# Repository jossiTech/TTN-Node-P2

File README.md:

# TTN-Node-P2
Based on Arduino Pro Micro 3.3V & RFM95W:  four 1-Wire-Busses - suitable enclosure available - messure Temperature, Humidity, ...

read more on the [Wiki](https://github.com/jossiTech/TTN-Node-P2/wiki)

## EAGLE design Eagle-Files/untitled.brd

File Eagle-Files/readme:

If you are interested in the original EAGLE-Files (*.brd and *.sch) feel free to contact me (info@jossitech.de)...
A suitable case is available in which the PCB fits perfectly. Search for "strapubox 524"

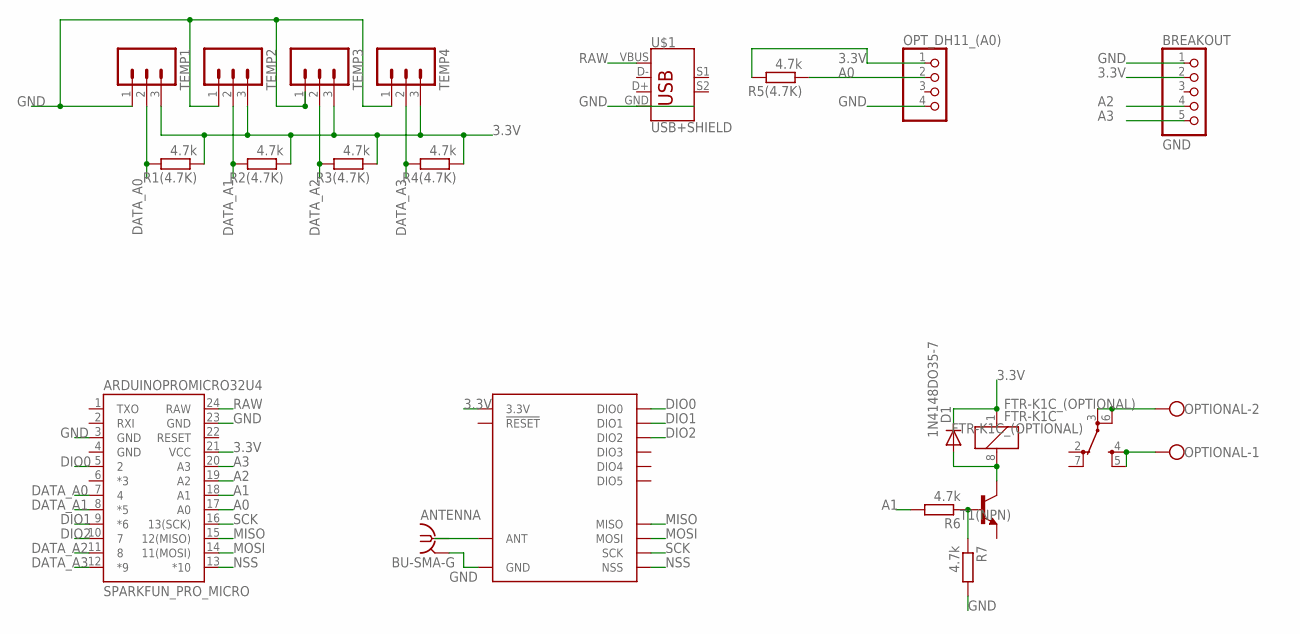
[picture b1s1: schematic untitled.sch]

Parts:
ANTENNA: BU-SMA-G
ARDUINOPROMICRO32U4: SPARKFUN_PRO_MICRO
BREAKOUT: GND; 1X05
D1: 1N4148DO35-7; DO35-7
FTR-K1C_(OPTIONAL): FTR-K1C
OPTIONAL: W237-102
OPT_DH11_(A0): PINHD-1X4; 1X04
R1(4.7K), R2(4.7K), R3(4.7K), R4(4.7K), R5(4.7K), R6, R7: 4.7k; 0207/10
T1(NPN): BC237-NPN-TO92-CBE; TO92-CBE
TEMP1, TEMP2, TEMP3, TEMP4: M03; 03P
U2: RFM95W; RFM95/96/97/98W
U$1: USB+SHIELD; USB-B-PTH

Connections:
3.3V: ARDUINOPROMICRO32U4.21 (VCC), BREAKOUT.2, D1.C, FTR-K1C_(OPTIONAL).1, OPT_DH11_(A0).1, R1(4.7K).1, R2(4.7K).1, R3(4.7K).1, R4(4.7K).1, R5(4.7K).2, TEMP1.3, TEMP2.3, TEMP3.3, TEMP4.3, U2.3.3V
A0: ARDUINOPROMICRO32U4.17 (A0), OPT_DH11_(A0).2, R5(4.7K).1
A1: ARDUINOPROMICRO32U4.18 (A1), R6.2
A2: ARDUINOPROMICRO32U4.19 (A2), BREAKOUT.4
A3: ARDUINOPROMICRO32U4.20 (A3), BREAKOUT.5
DATA_A0: ARDUINOPROMICRO32U4.7 (4), R1(4.7K).2, TEMP1.2
DATA_A1: ARDUINOPROMICRO32U4.8 (*5), R2(4.7K).2, TEMP2.2
DATA_A2: ARDUINOPROMICRO32U4.11 (8), R3(4.7K).2, TEMP3.2
DATA_A3: ARDUINOPROMICRO32U4.12 (*9), R4(4.7K).2, TEMP4.2
DIO0: ARDUINOPROMICRO32U4.5 (2), U2.DIO0
DIO1: ARDUINOPROMICRO32U4.9 (*6), U2.DIO1
DIO2: ARDUINOPROMICRO32U4.10 (7), U2.DIO2
GND: ANTENNA.2, ANTENNA.3 (2), ANTENNA.4 (2), ANTENNA.5 (2), ARDUINOPROMICRO32U4.3 (GND), ARDUINOPROMICRO32U4.4 (GND), ARDUINOPROMICRO32U4.23 (GND), BREAKOUT.1, OPT_DH11_(A0).4, R7.2, TEMP1.1, TEMP2.1, TEMP3.1, TEMP4.1, U2.GND@1 (GND), U2.GND@2 (GND), U2.GND@3 (GND), U$1.GND
MISO: ARDUINOPROMICRO32U4.15 (12(MISO)), U2.MISO
MOSI: ARDUINOPROMICRO32U4.14 (11(MOSI)), U2.MOSI
unnamed: ANTENNA.1, U2.ANT
unnamed: D1.A, FTR-K1C_(OPTIONAL).8 (2), T1(NPN).C
unnamed: R6.1, R7.1, T1(NPN).B
unnamed: FTR-K1C_(OPTIONAL).4 (SA), FTR-K1C_(OPTIONAL).5 (SB), OPTIONAL.1
unnamed: FTR-K1C_(OPTIONAL).3 (PA), FTR-K1C_(OPTIONAL).6 (PB), OPTIONAL.2
NSS: ARDUINOPROMICRO32U4.13 (*10), U2.NSS
RAW: ARDUINOPROMICRO32U4.24 (RAW), U$1.VBUS
SCK: ARDUINOPROMICRO32U4.16 (13(SCK)), U2.SCK

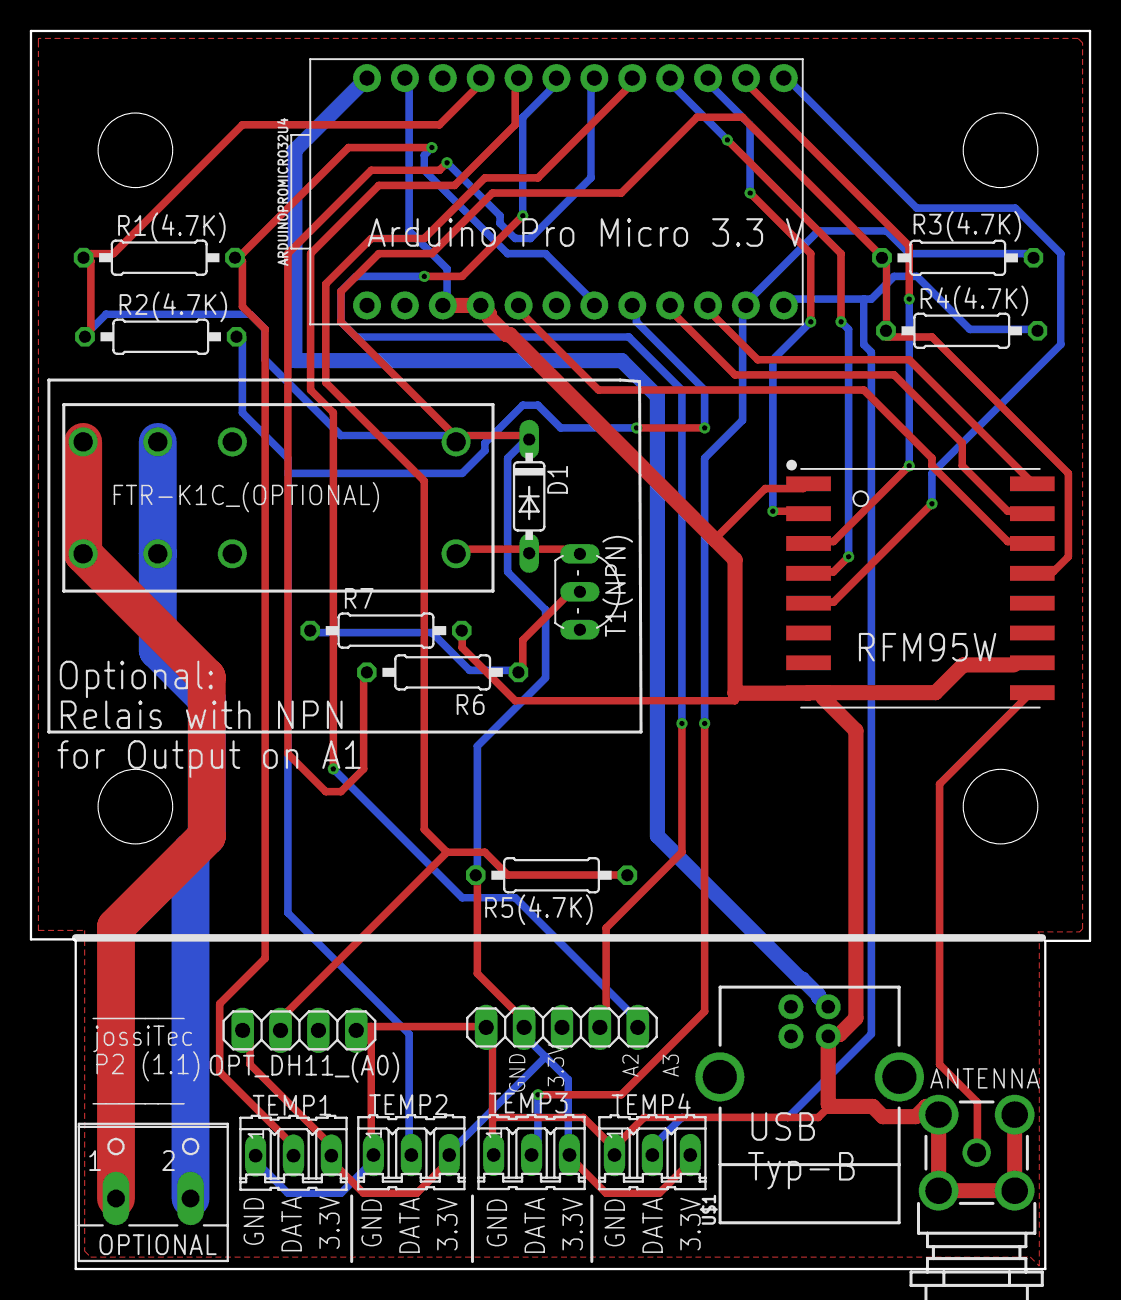
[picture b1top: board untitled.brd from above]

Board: 2 copper layers, 71.0 x 83.0 mm, 21 parts (0 on the bottom side), 23 nets.

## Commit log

2019-03-06 add eagle files
2019-03-06 change pcb-pdf
2019-03-07 PIC upload
2019-03-07 change size
2019-03-07 change pic
2019-03-07 add code
2019-03-11 add images
2019-03-14 add image overview
2019-03-14 images changes
2019-03-14 image change

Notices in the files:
parts and their libraries:
SparkFun-RF: Licensing: Creative Commons ShareAlike 4.0 International - https://creativecommons.org/licenses/by-sa/4.0
